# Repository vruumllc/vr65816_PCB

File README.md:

# vr65816

WDC 65C816 Single Board Retro-Computer compatible with [Rumbledethump's Picocomputer Architecture](https://picocomputer.github.io/)

This project is based on [Rumbledethump's Picocomputer 6502 design](https://github.com/picocomputer/schematic), so he gets top billing. 

That said, any flaws are my fault, 'cause his board works GREAT! 

Report any problems to me using the ['Issues'](https://github.com/vruumllc/vr65816_schematic/issues) menu item above.

## Is the vr65816 for you?
Should you be building the vr65816 at all? This board is targeted at experienced programmers interested in exploring and exploiting the 65816 microprocessor. You might want to read the [Caveats](https://github.com/vruumllc/vr65816_schematic/blob/main/README.md#caveats) section at the end of this document before continuing. I built it because I wanted to create projects requiring more memory than the 64kB limit of the 8-bit 6502 processor, and I'm willing to experiment, and fail. 

If you aren't an experienced programmer, or just want to build an inexpensive but extremely capable retro-computer to re-live the exciting early days of the personal computer, then I'd strongly suggest starting with the Rumbledethump's Picocomputer 6502 (RP6502 for short). Order a PCB and support his project [here](https://ko-fi.com/rumbledethumps). 

## My goals for this project
- Use 2 [Rasberry Pi Pico2s](https://www.raspberrypi.com/products/raspberry-pi-pico-2/) with [Rumbledethumps' rp6502 firmware](https://github.com/picocomputer/rp6502)
- Run [WDC 65C816](https://www.westerndesigncenter.com/wdc/documentation/w65c816s.pdf) at up to 8Mhz, clocked by Pico2W RIA
- Use currently produced through-hole ICs only, and no programmable logic
- Use 1MB SRAM, 64kB extended RAM (on Pico2W RIA), and no hardware ROM
- Use [WDC 65C22](https://www.westerndesigncenter.com/wdc/documentation/w65c22s.pdf) for timers and peripheral I/O
- Design, [breadboard](https://github.com/vruumllc/vr65816_schematic/blob/main/images/vr65816_breadboard.jpg), and test it. 
- Run all existing apps and games ("[ROMs](https://discord.com/channels/534571197908647946/1487969279251841216)") for the Rumbledethumps' RP6502 Picocomputer
- Enable [creation](https://github.com/picocomputer/rp6502-sdk) of new "ROMs" utilizing [features and memory of the '816](https://archive.org/details/0893037893ProgrammingThe65816/mode/2up)
- Use [KiCad](https://www.kicad.org/download) to create fully open source schematic and board design files

## Getting the parts
I used [Mouser's 'Create a BOM'](https://www.mouser.com/en/Bom/) feature to order all parts except the PCB.  Use the 'Mouser Part Number' and 'Qty' columns from the [vr65816_full_BOM.csv](https://github.com/vruumllc/vr65816_schematic/blob/main/vr65816_full_BOM.csv) file in this repository.

You can also get the identical parts at [DigiKey](https://www.digikey.com/), except for the WDC 65C816 and 65C22.

My cost per kit of parts was about $124 USD, including shipping, fees, and taxes.

## Getting a PCB
I used [PCBWay](https://www.pcbway.com) to fabricate my PCB:
- Click on "PCB Prototype" at upper left after logging in
- Enter Length=125 and Width=150 mm for the Size
- Select Quantity desired (5 minimum)
- Select Solder Mask and Silkscreen Colors, Surface Finish, and 'Remove Product No.' as desired
- Press the 'Calculate' button at the bottom to generate a price quote
- If the price is right, press 'Save to Cart', then 'Agree' buttons
- Drag the [vr65816_gerbers.zip](https://github.com/vruumllc/vr65816_schematic/blob/main/vr65816_gerbers.zip) file into the web dialog, then click 'Submit the file now'

After a wait of a few minutes while the file is 'Under Review' you will be allowed to place your order.

My cost was about $105 USD including shipping, fees, and taxes -- about $21 USD per PCB.

The total price per vr65816 therefore came out to be about $145 USD (September 2026, Silicon Valley, USA).

## More things you need that you may already own
Rumbledethumps has made a huge effort to support modern hardware, so you don't have to rely on ancient and expensive peripherals to use this retro-computer. Here is a list of peripherals you may already have, with some example links if you don't:

(All links are just clarifying examples and not an endorsement or guarantee of compatibility)

- USB micro-B cable with either [A](https://www.adafruit.com/product/592) or [C](https://www.adafruit.com/product/3878) connector (depending upon what your desktop or laptop computer has)
- [USB-OTG Hub with micro-B connector](https://vilros.com/products/vilros-microusb-to-usb-4-port-otg-hub-black-great-for-pi-zero)
- USB2 flash drive formatted for FAT32 (or 'msdos' in Linux)
- Keyboard, Mouse and [Gamepad](https://www.logitechg.com/en-us/shop/p/f310-gamepad) (USB-2 cable or [wireless](https://www.logitech.com/en-us/shop/p/mk470-slim-wireless-keyboard-mouse), or Bluetooth LE)
- Stereo headphones or computer speakers
- VGA Monitor and cable

  OR
  
- HDMI Monitor, cable, and [VGA to HDMI adapter](https://ventiontech.com/products/vga-to-hdmi-adapter-1080p-vga-male-to-hdmi-female-converter-cable-with-audio-usb-power-for-ps4-3-hdtv-vga-hdmi-converter) (NOT HDMI to VGA adapter!!!)

## Building the vr65816 
On a scale from 1 to 10 for electronics kit build difficulty, the vr65816 ranks about a 3. While it is probably not the best project to learn soldering on, it is an easy kit to build -- well within the capabilities of a supervised middle-school student. The component identifications are all on the back of the PCB, and listed in the [BOM](https://github.com/vruumllc/vr65816_schematic/blob/main/vr65816_full_BOM.csv).

The hardest part is making sure you have the right resisters in the right places (consult a [resister color key](https://en.wikipedia.org/wiki/Electronic_color_code), or use an Ohm meter to make sure). Other than that, just make sure your sockets (and the chips inserted in them) are the correct direction as indicated by the notch on the PCB, and that the 2 LEDs are soldered with the shorter leg (with the flat) in the hole with the square solder pad (cathode in pin1). I guess the middle row of the VGA connector might be a little tricky if you don't have a fine tipped soldering iron...but...you can do this! 

## Uploading the Picocomputer firmware
Get the latest released firmware from [here](https://github.com/picocomputer/rp6502/releases). You want the file named rp6502-#.##-pico.zip, where #.## is the latest version number. 
- Unzip the files to a temporary folder on your host computer
- Plug the micro-B USB cable into the Pico 2W (the one with the rectangular metal shield around the wireless chip)
- Press and hold the BootSel button on the Pico 2W, then plug the other end of the cable into your host computer
- Release the BootSel button, and you should see a new drive appear on your host computer
- Copy (or drag) the rp6502-#.##-ria-w.uf2 file into the new drive
- The file should upload to the Pico 2W and turn it into the "RIA", lighting the LED.
- Repeat the process for the Pico 2, this time copying the rp6502-#.##-vga.uf2, creating the 'VGA card' for the vr65816.
- Unplug the USB cable from your host computer, leaving it connected to the Pico 2 VGA micro-B port

## Testing your vr65816
OK! You should now have a completed vr65816 retro-computer of your very own. Let's test it.
- Plug the USB 2 OTG hub into the micro-B port of the Pico 2W RIA
- On your host computer, copy the [test "ROM" files](https://github.com/vruumllc/vr65816_schematic/tree/main/test_ROMS) (ending in .rp6502 or .vr65816) from this repository into the USB flash drive
- Remove the USB flash drive from your host computer and plug it into the USB 2 OTG hub
- Plug in any other USB 2 peripherals like keyboard, mouse, and gamepad, if you have them
- Plug in the headphones or computer speakers, if you have them
- Plug in the video monitor if you have it, using the VGA to HDMI adapter if it is an HDMI monitor
- Finally, plug the USB cable connected to the Pico 2 VGA back into your host computer.

If you have a video monitor connected, you should see "Picocomputer 6502" and the RIA and VGA firmware versions you uploaded, followed by the prompt ']' and a blinking cursor.

If you don't have monitor, keyboard, mouse, gamepad, or speakers yet, don't worry.  You can still continue testing as long as you have the USB cable connected from the Pico 2 VGA to your host computer.  Besides powering the vr65816, this cable supplies a serial communication channel operating at 115200 baud, 8 data bits, 1 stop bit, no parity, and no flow control. You can use a serial terminal program on your host computer to interact with the vr65816. The details vary depending upon your host computer type. I use Linux and like GTKTerm. PuttySSH also works well and exists for both Linux and Windows. Sorry, I've never owned a Mac, so you are on your own.

If you've arrived at the ']', you've verified that the Pico half of the vr65816 is working.  You are looking at the prompt for the 'monitor' program (not to be confused with a computer display), which runs on the Pico 2W RIA. Try typing "help" to see all that it can do for you. 

You still haven't tested the 65816 half of the board, however. To do that, simply type "0" and return.  You should see the contents of the first 16 bytes of the 65816 memory, thus verifying that the RIA can talk to the 65816 microprocessor and access its memory.

Congratulations! Time to start having fun by loading some ROMs.

## Caveats
Rumbledethump's Picocomputer Architecture for the WDC 65C02 was developed over several YEARS and encompasses not just the RP6502 hardware and its firmware, but platform support on two C compilers, and a programming infrastructure developed for Microsoft's Visual Studio Code IDE (not to mention the emulators, FPGA implementation...).

All of this is a wonderful base for my project, but I went into it knowing that since it was developed for the 6502, that there would some limitations re-using it. I had NO intentions of forking any of his architecture, and instead would learn to work within the limitations. You should too. 

Here are some things to keep in mind before building my vr65816:

1. Rumbledethump has stated that he has no interest in the 65816. That means the vr65816 is a kind of a, umm, love child of his efforts. Please don't ask him to add any new features in support of this project.
2. Similarly, be considerate at the [Picocomputer 6502 Discord site](https://discord.com/channels/534571197908647946/1545859287706902559). Rumbledethumps has created an '#other-hardware' channel for projects like mine. Please use it. I'll keep on eye on it.
3. Very importantly, neither C compiler supporting the RP6502 compiles for the 65816. The ca65 assembler piece of the [cc65 project](https://cc65.github.io/) DOES understand 65816 assembly, though, as does [llvm-mos's](https://llvm-mos.org/wiki/Welcome) assembler. This means that to exploit the 16-bit features and memory of the vr65816, you will need to code in assembly language. I plan to put 'best practice' examples in the [vr65816_examples](https://github.com/vruumllc/vr65816_examples) repository. I could really use help developing these, as I know relatively little about assembly language programming.
4. Unfortunately, the 6502 memory locations reserved for the 'RIA registers', used to communicate between the Pico 2W RIA and the 6502, overlap the 65816 16-bit interrupt vectors. That limits us to throwing interrupts only while in 8-bit mode. As a very last resort, I added the mysterious jumper JP4, which increases the space for the RIA registers enough to shift them down. This would mean #defining all the register locations in the firmware and compilers, and breaking compatibility with 6502 ROMs, which I really, really, really don't want to do.
5. The RIA can only access the lowest 64kB of memory, so each 65816 ROM will have to be responsible for loading its assets and code into higher memory. Large 65816 projects will need to be designed so that the initially loaded portion is less than 64kB.
6. 65816 ROMs will have to check programatically to make sure they are not accidentally loaded into an RP6502. The ROMS must exit gracefully with a message if so. The monitor program handles loading ROMs renamed to have a .vr65816 extension, so that might help to avoid confusion.
7. The monitor program can only dump the lowest 64kB of microcontroller memory (65816 Bank0), and displays the 64kB of extended RAM living on the RIA using the 65816 Bank1 addresses. Confusing, but if dumping any 65816 upper memory is needed, a 65816-specific ROM can be written.
8. The emulators written thus far only support the RP6502.
9. The vr65816 PCB is 25mm taller than the RP6502 PCB, so it won't fit in the fabulous 3D-printed cases I've already designed. If I ever finish working on this README and the vr65816_examples, I'll hop right to it and come up with something special.
10. I'm sure more things will come to light...

Don't get too discouraged by all this. At the very least you'll wind up with a retro-computer compatible with the RP6502, which (have I already mentioned this?) is really GREAT!

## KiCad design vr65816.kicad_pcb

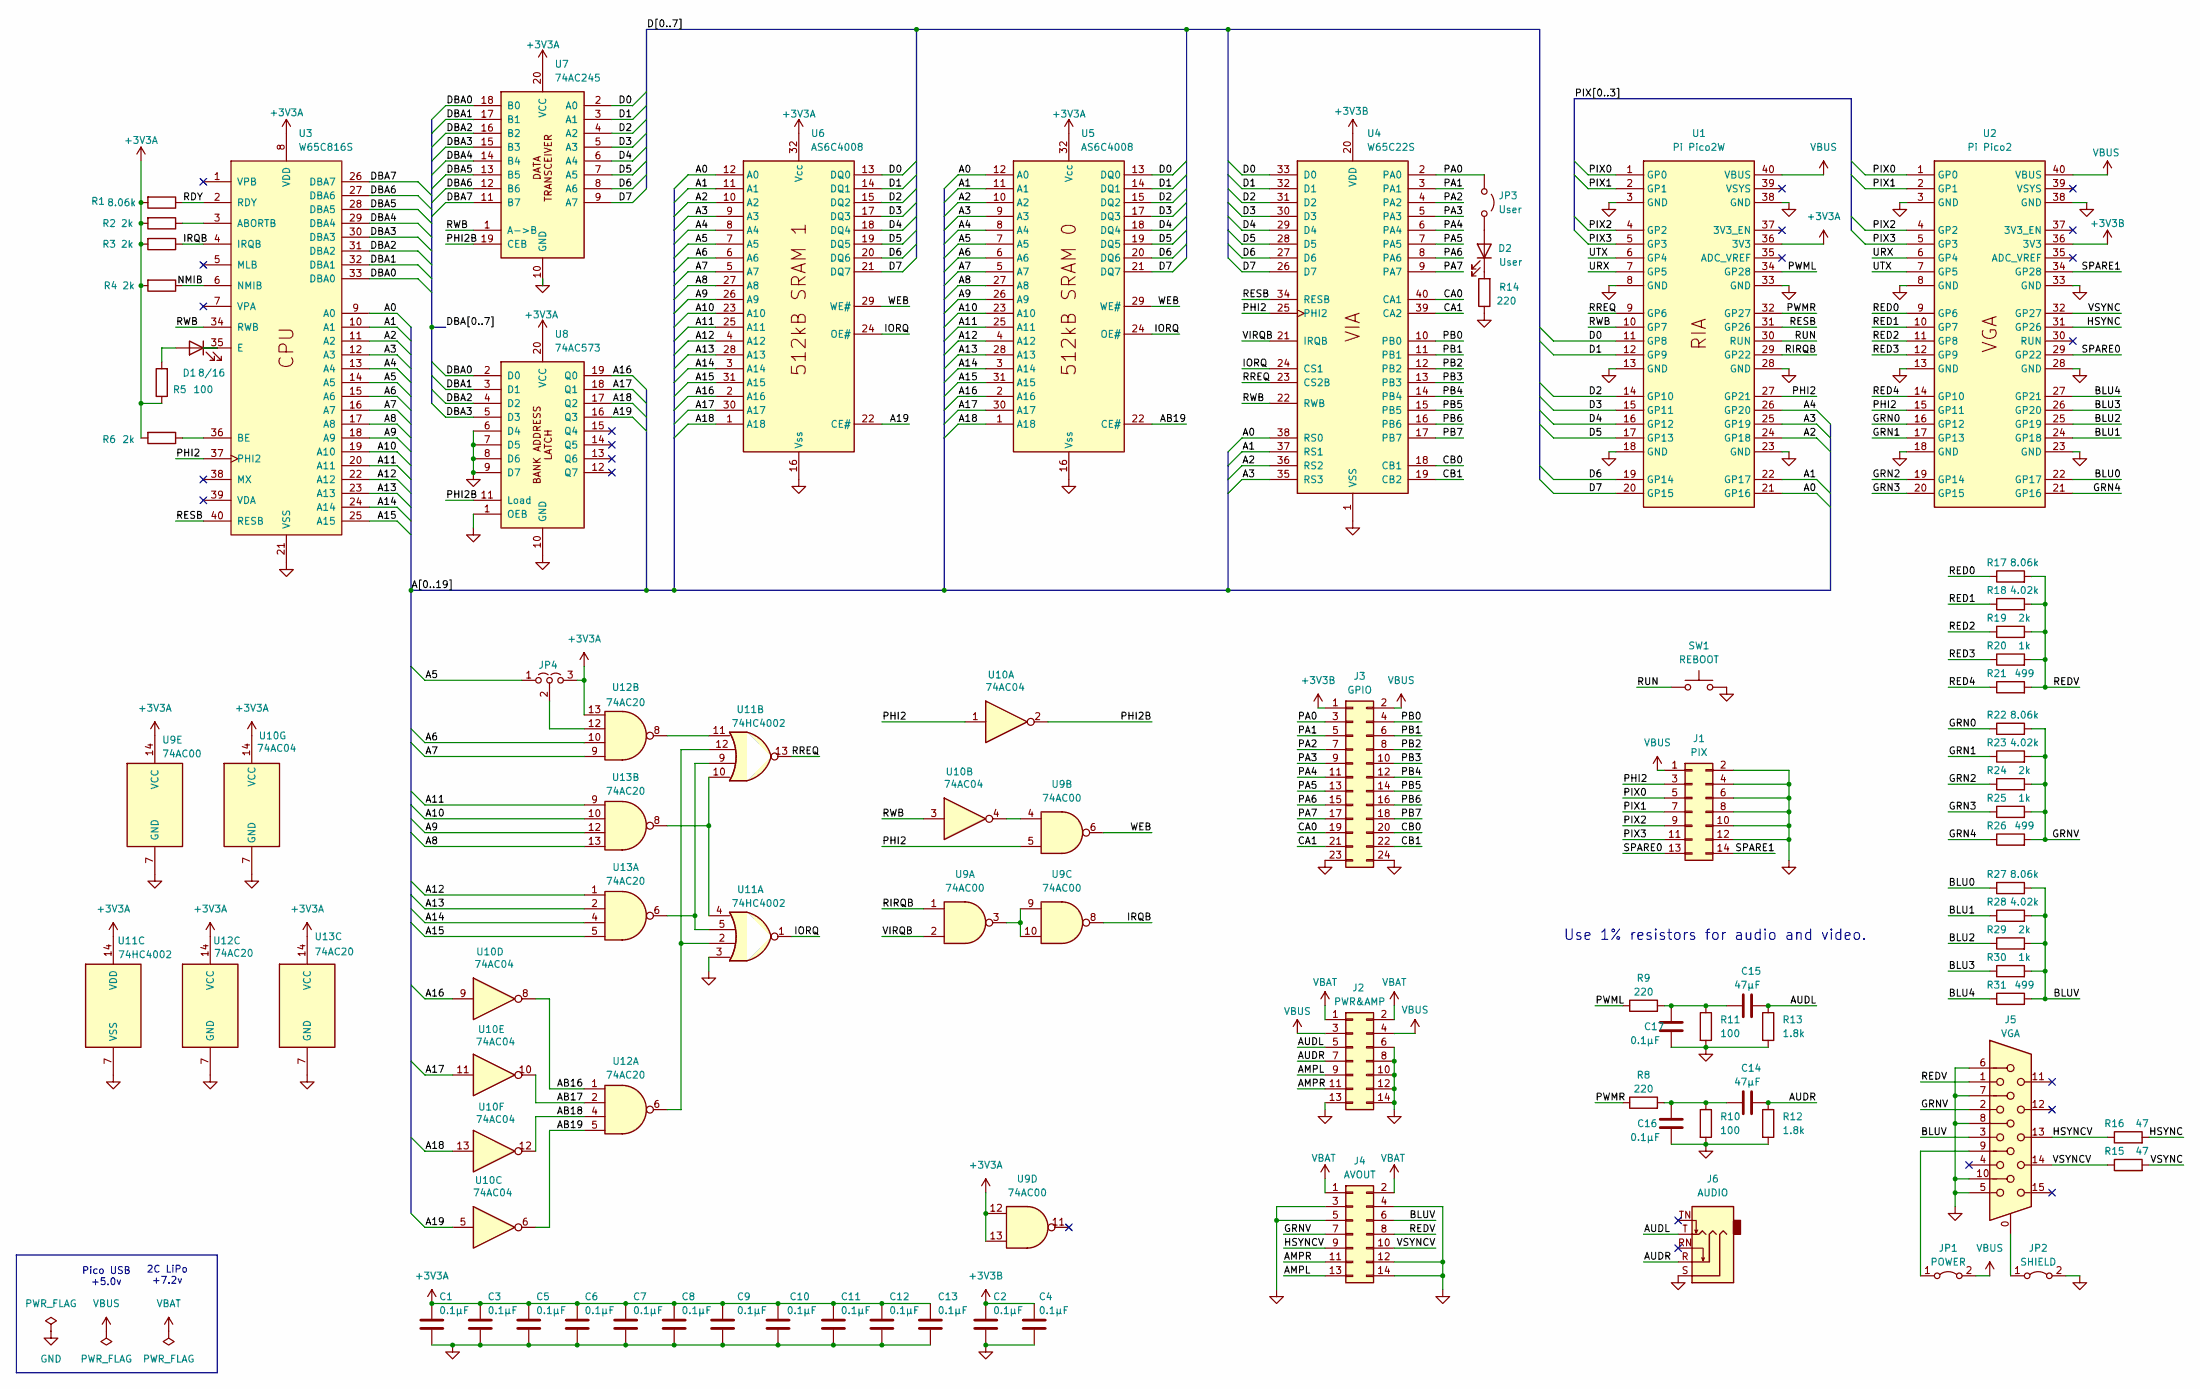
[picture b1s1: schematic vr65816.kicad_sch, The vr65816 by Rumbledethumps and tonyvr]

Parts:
C1, C2, C3, C4, C5, C6, C7, C8, C9, C10, C11, C12, C13, C16, C17: 0.1μF; R_Axial_DIN0207_L6.3mm_D2.5mm_P10.16mm_Horizontal_Long
C14, C15: 47μF; C_Disc_D7.5mm_W5.0mm_P5.00mm_Long
D1: 8/16; LED_D3.0mm
D2: User; LED_D3.0mm
J1: PIX; PinHeader_2x07_P2.54mm_Vertical
J2: PWR&AMP; PinHeader_2x07_P2.54mm_Vertical
J3: GPIO; PinHeader_2x12_P2.54mm_Vertical
J4: AVOUT; PinHeader_2x07_P2.54mm_Vertical
J5: VGA; DSUB-15-HD_Female_Horizontal_P2.29x2.54mm_EdgePinOffset8.35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
J6: AUDIO; Jack_3.5mm_CUI_SJ1-3525N_Horizontal
JP1: POWER; SolderJumper-2_P1.3mm_Bridged2Bar_RoundedPad1.0x1.5mm
JP2: SHIELD; SolderJumper-2_P1.3mm_Bridged2Bar_RoundedPad1.0x1.5mm
JP3: User; PinHeader_1x02_P2.54mm_Vertical
JP4: 3,[2,1]; PinHeader_1x03_P2.54mm_Vertical
R1, R17, R22, R27: 8.06k; R_Axial_DIN0207_L6.3mm_D2.5mm_P10.16mm_Horizontal_Long
R2, R3, R4, R6, R19, R24, R29: 2k; R_Axial_DIN0207_L6.3mm_D2.5mm_P10.16mm_Horizontal_Long
R5, R10, R11: 100; R_Axial_DIN0207_L6.3mm_D2.5mm_P10.16mm_Horizontal_Long
R8, R9, R14: 220; R_Axial_DIN0207_L6.3mm_D2.5mm_P10.16mm_Horizontal_Long
R12, R13: 1.8k; R_Axial_DIN0207_L6.3mm_D2.5mm_P10.16mm_Horizontal_Long
R15, R16: 47; R_Axial_DIN0207_L6.3mm_D2.5mm_P10.16mm_Horizontal_Long
R18, R23, R28: 4.02k; R_Axial_DIN0207_L6.3mm_D2.5mm_P10.16mm_Horizontal_Long
R20, R25, R30: 1k; R_Axial_DIN0207_L6.3mm_D2.5mm_P10.16mm_Horizontal_Long
R21, R26, R31: 499; R_Axial_DIN0207_L6.3mm_D2.5mm_P10.16mm_Horizontal_Long
SW1: REBOOT; SW_Tactile_SKHH_Angled
U1: Pi Pico2W; DIP-40_W17.78mm_LongPads
U2: Pi Pico2; DIP-40_W17.78mm_LongPads
U3: W65C816S; DIP-40_W15.24mm_LongPads
U4: W65C22S; DIP-40_W15.24mm_LongPads
U5, U6: AS6C4008; DIP-32_W15.24mm_LongPads
U7: 74AC245; DIP-20_W7.62mm_LongPads
U8: 74AC573; DIP-20_W7.62mm_LongPads
U9: 74AC00; DIP-14_W7.62mm_LongPads
U10: 74AC04; DIP-14_W7.62mm_LongPads
U11: 74HC4002; DIP-14_W7.62mm_LongPads
U12, U13: 74AC20; DIP-14_W7.62mm_LongPads

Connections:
+3V3A: C1.1, C3.1, C5.1, C6.1, C7.1, C8.1, C9.1, C10.1, C11.1, C12.1, C13.1, JP4.3 (B), R1.2, R2.2, R3.2, R4.2, R5.1, R6.2, U1.36 (3V3), U3.8 (VDD), U5.32 (Vcc), U6.32 (Vcc), U7.20 (VCC), U8.20 (VCC), U9.12, U9.13, U9.14 (VCC), U10.14 (VCC), U11.14 (VDD), U12.13, U12.14 (VCC), U13.14 (VCC)
+3V3B: C2.1, C4.2, J3.1, U2.36 (3V3), U4.20 (VDD)
/A0: U1.21 (GP16), U3.9 (A0), U4.38 (RS0), U5.12 (A0), U6.12 (A0)
/A1: U1.22 (GP17), U3.10 (A1), U4.37 (RS1), U5.11 (A1), U6.11 (A1)
/A2: U1.24 (GP18), U3.11 (A2), U4.36 (RS2), U5.10 (A2), U6.10 (A2)
/A3: U1.25 (GP19), U3.12 (A3), U4.35 (RS3), U5.9 (A3), U6.9 (A3)
/A4: U1.26 (GP20), U3.13 (A4), U5.8 (A4), U6.8 (A4)
/A5: JP4.1 (A), U3.14 (A5), U5.7 (A5), U6.7 (A5)
/A6: U3.15 (A6), U5.6 (A6), U6.6 (A6), U12.10
/A7: U3.16 (A7), U5.5 (A7), U6.5 (A7), U12.9
/A8: U3.17 (A8), U5.27 (A8), U6.27 (A8), U13.13
/A9: U3.18 (A9), U5.26 (A9), U6.26 (A9), U13.12
/A10: U3.19 (A10), U5.23 (A10), U6.23 (A10), U13.10
/A11: U3.20 (A11), U5.25 (A11), U6.25 (A11), U13.9
/A12: U3.22 (A12), U5.4 (A12), U6.4 (A12), U13.1
/A13: U3.23 (A13), U5.28 (A13), U6.28 (A13), U13.2
/A14: U3.24 (A14), U5.3 (A14), U6.3 (A14), U13.4
/A15: U3.25 (A15), U5.31 (A15), U6.31 (A15), U13.5
/A16: U5.2 (A16), U6.2 (A16), U8.19 (Q0), U10.9
/A17: U5.30 (A17), U6.30 (A17), U8.18 (Q1), U10.11
/A18: U5.1 (A18), U6.1 (A18), U8.17 (Q2), U10.13
/A19: U6.22 (CE#), U8.16 (Q3), U10.5
/AB16: U10.8, U12.1
/AB17: U10.10, U12.2
/AB18: U10.12, U12.4
/AB19: U5.22 (CE#), U10.6, U12.5
/AMPL: J2.9, J4.13
/AMPR: J2.11, J4.11
/AUDL: C15.2, J2.5, J6.T, R13.1
/AUDR: C14.2, J2.7, J6.R, R12.1
/BLU0: R27.1, U2.22 (GP17)
/BLU1: R28.1, U2.24 (GP18)
/BLU2: R29.1, U2.25 (GP19)
/BLU3: R30.1, U2.26 (GP20)
/BLU4: R31.1, U2.27 (GP21)
/BLUV: J4.6, J5.3, R27.2, R28.2, R29.2, R30.2, R31.2
/CA0: J3.19, U4.40 (CA1)
/CA1: J3.21, U4.39 (CA2)
/CB0: J3.20, U4.18 (CB1)
/CB1: J3.22, U4.19 (CB2)
/D0: U1.11 (GP8), U4.33 (D0), U5.13 (DQ0), U6.13 (DQ0), U7.2 (A0)
/D1: U1.12 (GP9), U4.32 (D1), U5.14 (DQ1), U6.14 (DQ1), U7.3 (A1)
/D2: U1.14 (GP10), U4.31 (D2), U5.15 (DQ2), U6.15 (DQ2), U7.4 (A2)
/D3: U1.15 (GP11), U4.30 (D3), U5.17 (DQ3), U6.17 (DQ3), U7.5 (A3)
/D4: U1.16 (GP12), U4.29 (D4), U5.18 (DQ4), U6.18 (DQ4), U7.6 (A4)
/D5: U1.17 (GP13), U4.28 (D5), U5.19 (DQ5), U6.19 (DQ5), U7.7 (A5)
/D6: U1.19 (GP14), U4.27 (D6), U5.20 (DQ6), U6.20 (DQ6), U7.8 (A6)
/D7: U1.20 (GP15), U4.26 (D7), U5.21 (DQ7), U6.21 (DQ7), U7.9 (A7)
/DBA0: U3.33 (DBA0), U7.18 (B0), U8.2 (D0)
/DBA1: U3.32 (DBA1), U7.17 (B1), U8.3 (D1)
/DBA2: U3.31 (DBA2), U7.16 (B2), U8.4 (D2)
/DBA3: U3.30 (DBA3), U7.15 (B3), U8.5 (D3)
/DBA4: U3.29 (DBA4), U7.14 (B4)
/DBA5: U3.28 (DBA5), U7.13 (B5)
/DBA6: U3.27 (DBA6), U7.12 (B6)
/DBA7: U3.26 (DBA7), U7.11 (B7)
/GRN0: R22.1, U2.16 (GP12)
/GRN1: R23.1, U2.17 (GP13)
/GRN2: R24.1, U2.19 (GP14)
/GRN3: R25.1, U2.20 (GP15)
/GRN4: R26.1, U2.21 (GP16)
/GRNV: J4.7, J5.2, R22.2, R23.2, R24.2, R25.2, R26.2
/HSYNC: R16.2, U2.31 (GP26)
/HSYNCV: J4.9, J5.13, R16.1
/IORQ: U4.24 (CS1), U5.24 (OE#), U6.24 (OE#), U11.1
/IRQB: R3.1, U3.4 (IRQB), U9.8
/NMIB: R4.1, U3.6 (NMIB)
/PA0: J3.3, JP3.1 (A), U4.2 (PA0)
/PA1: J3.5, U4.3 (PA1)
/PA2: J3.7, U4.4 (PA2)
/PA3: J3.9, U4.5 (PA3)
/PA4: J3.11, U4.6 (PA4)
/PA5: J3.13, U4.7 (PA5)
/PA6: J3.15, U4.8 (PA6)
/PA7: J3.17, U4.9 (PA7)
/PB0: J3.4, U4.10 (PB0)
/PB1: J3.6, U4.11 (PB1)
/PB2: J3.8, U4.12 (PB2)
/PB3: J3.10, U4.13 (PB3)
/PB4: J3.12, U4.14 (PB4)
/PB5: J3.14, U4.15 (PB5)
/PB6: J3.16, U4.16 (PB6)
/PB7: J3.18, U4.17 (PB7)
/PHI2: J1.3, U1.27 (GP21), U2.15 (GP11), U3.37 (PHI2), U4.25 (PHI2), U9.5, U10.1
/PHI2B: U7.19 (CEB), U8.11 (Load), U10.2
/PIX0: J1.5, U1.1 (GP0), U2.1 (GP0)
/PIX1: J1.7, U1.2 (GP1), U2.2 (GP1)
/PIX2: J1.9, U1.4 (GP2), U2.4 (GP2)
/PIX3: J1.11, U1.5 (GP3), U2.5 (GP3)
/PWML: R9.1, U1.34 (GP28)
/PWMR: R8.1, U1.32 (GP27)
/RDY: R1.1, U3.2 (RDY)
/RED0: R17.1, U2.9 (GP6)
/RED1: R18.1, U2.10 (GP7)
/RED2: R19.1, U2.11 (GP8)
/RED3: R20.1, U2.12 (GP9)
/RED4: R21.1, U2.14 (GP10)
/REDV: J4.8, J5.1, R17.2, R18.2, R19.2, R20.2, R21.2
/RESB: U1.31 (GP26), U3.40 (RESB), U4.34 (RESB)
/RIRQB: U1.29 (GP22), U9.1
/RREQ: U1.9 (GP6), U4.23 (CS2B), U11.13
/RUN: SW1.2, U1.30 (RUN)
/RWB: U1.10 (GP7), U3.34 (RWB), U4.22 (RWB), U7.1 (A->B), U10.3
/SPARE0: J1.13, U2.29 (GP22)
/SPARE1: J1.14, U2.34 (GP28)
/URX: U1.7 (GP5), U2.6 (GP4)
/UTX: U1.6 (GP4), U2.7 (GP5)
/VIRQB: U4.21 (IRQB), U9.2
/VSYNC: R15.2, U2.32 (GP27)
/VSYNCV: J4.10, J5.14, R15.1
/WEB: U5.29 (WE#), U6.29 (WE#), U9.6
GND: C1.2, C2.2, C3.2, C4.1, C5.2, C6.2, C7.2, C8.2, C9.2, C10.2, C11.2, C12.2, C13.2, C16.2, C17.2, J1.2, J1.4, J1.6, J1.8, J1.10, J1.12, J2.6, J2.8, J2.10, J2.12, J2.13, J2.14, J3.23, J3.24, J4.3, J4.4, J4.5, J4.12, J4.14, J5.5, J5.6, J5.7, J5.8, J5.10, J6.S, JP2.2 (B), R10.2, R11.2, R12.2, R13.2, R14.1, SW1.1, U1.3 (GND), U1.8 (GND), U1.13 (GND), U1.18 (GND), U1.23 (GND), U1.28 (GND), U1.33 (GND), U1.38 (GND), U2.3 (GND), U2.8 (GND), U2.13 (GND), U2.18 (GND), U2.23 (GND), U2.28 (GND), U2.33 (GND), U2.38 (GND), U3.21 (VSS), U4.1 (VSS), U5.16 (Vss), U6.16 (Vss), U7.10 (GND), U8.1 (OEB), U8.6 (D4), U8.7 (D5), U8.8 (D6), U8.9 (D7), U8.10 (GND), U9.7 (GND), U10.7 (GND), U11.3, U11.7 (VSS), U12.7 (GND), U13.7 (GND)
unnamed: C14.1, C16.1, R8.2, R10.1
unnamed: C15.1, C17.1, R9.2, R11.1
unnamed: D1.2 (A), R5.2
unnamed: D1.1 (K), U3.35 (E)
unnamed: D2.2 (A), JP3.2 (B)
unnamed: D2.1 (K), R14.2
unnamed: J5.9, JP1.1 (A)
unnamed: J5.0, JP2.1 (A)
unnamed: JP4.2 (C), U12.12
unnamed: R2.1, U3.3 (ABORTB)
unnamed: R6.1, U3.36 (BE)
unnamed: U9.3, U9.9, U9.10
unnamed: U9.4, U10.4
unnamed: U11.5, U11.9, U13.6
unnamed: U11.4, U11.10, U13.8
unnamed: U11.11, U12.8
unnamed: U11.2, U11.12, U12.6
VBAT: J2.1, J2.2, J4.1, J4.2
VBUS: J1.1, J2.3, J2.4, J3.2, JP1.2 (B), U1.40 (VBUS), U2.40 (VBUS)

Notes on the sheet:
Use 1% resistors for audio and video.
Pico USB +5.0v
2C LiPo +7.2v

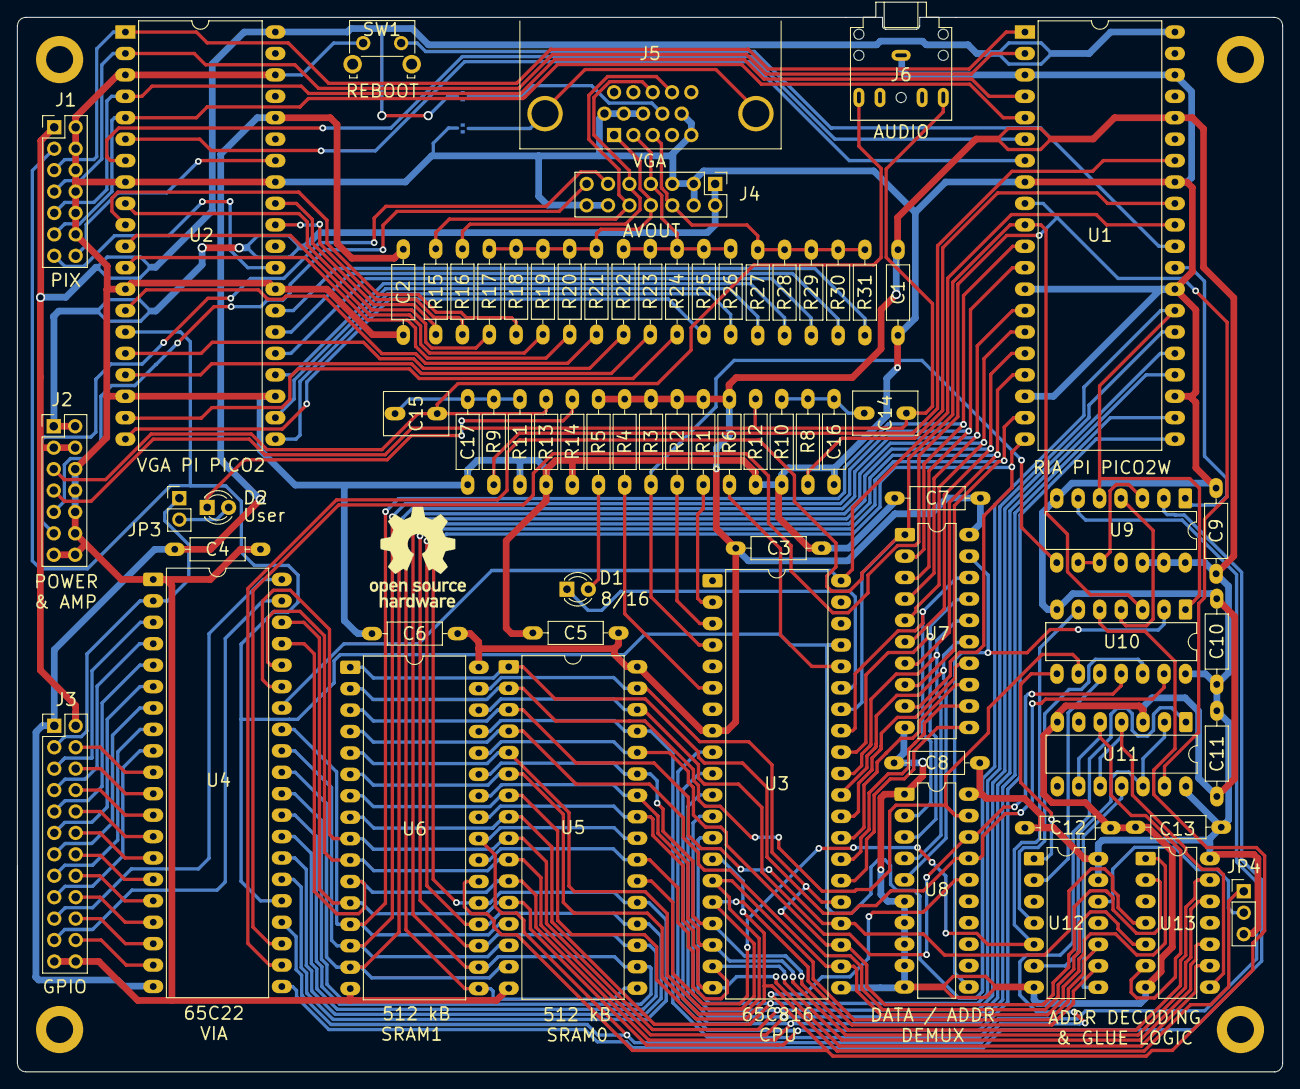
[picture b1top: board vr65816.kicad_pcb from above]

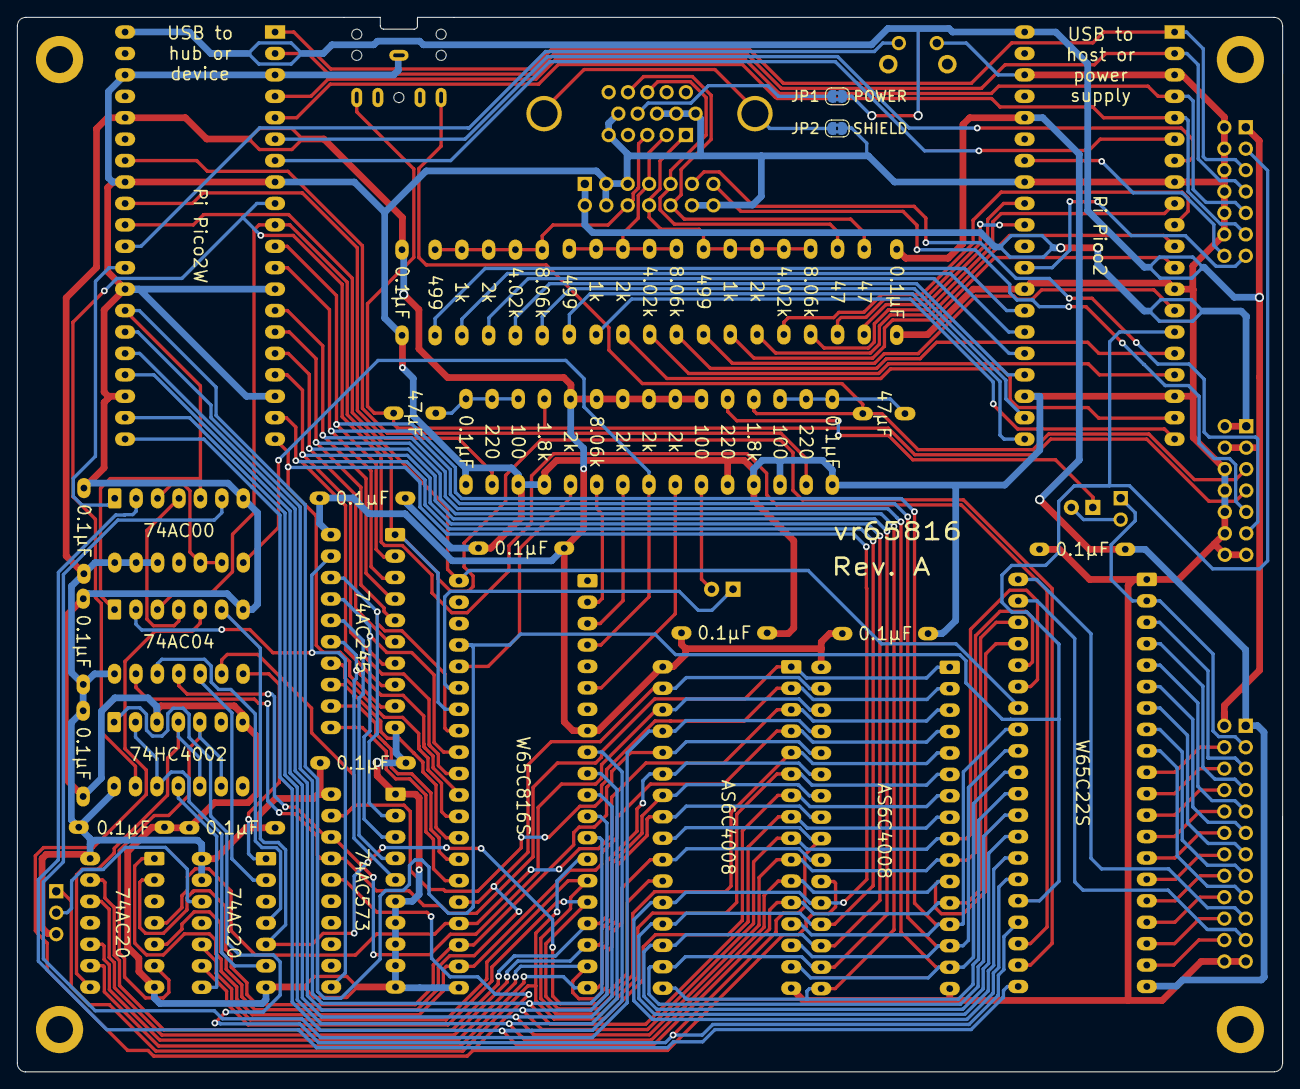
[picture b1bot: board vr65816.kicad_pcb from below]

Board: 2 copper layers, 150.0 x 125.0 mm, 73 parts (2 on the bottom side), 131 nets.

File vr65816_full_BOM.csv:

Qty,Reference,Description,Mfr Name,Mfr Part Number,Mouser Part Number
15,"C1, C2, C3, C4, C5, C6, C7, C8, C9, C10, C11, C12, C13, C16, C17",0.1μF Ceramic Capacitor,Vishay,A104M15X7RF5TAA,594-A104M15X7RF5TAA
2,"C14, C15",47μF Ceramic Capacitor,TDK,FG22X5R1A476MNT06,810-FG22X5R1A476MNT6
1,D1,"3.0mm LED, yellow",Vishay,TLLY4400,78-TLLY4400
1,D2,"3.0mm LED, green",Vishay,TLLG4400,78-TLLG4400
4,"R1,R17, R22, R27",8.06k resistor 1%,YAGEO,MFR-25FBF52-8K06,603-MFR-25FBF52-8K06
3,"R18, R23, R28",4.02k resistor 1%,YAGEO,MFR-25FBF52-4K02,603-MFR-25FBF52-4K02
7,"R2, R3, R4, R6, R19, R24, R29",2k resistor 1%,YAGEO,MFR-25FBF52-2K,603-MFR-25FBF52-2K
2,"R12, R13",1.8k resistor 1%,YAGEO,MFR-25FBF52-1K8,603-MFR-25FBF52-1K8
3,"R20, R25, R30",1k resistor 1%,YAGEO,MFR-25FBF52-1K,603-MFR-25FBF52-1K
3,"R21, R26, R31",499 ohm resistor 1%,YAGEO,MFR-25FBF52-499R,603-MFR-25FBF52-499R
3,"R8, R9, R14",220 ohm resistor 1%,YAGEO,MFR-25FBF52-220R,603-MFR-25FBF52-220R
3,"R5, R10, R11",100 ohm resistor 1%,YAGEO,MFR-25FBF52-100R,603-MFR-25FBF52-100R
2,"R15, R16",47 ohm resistor 1%,YAGEO,MFR-25FBF52-47R,603-MFR-25FBF52-47R
1,U3,WDC W65C816S,WDC,W65C816S6PG-14,955-W65C816S6PG-14
1,U4,WDC W65C22S,WDC,W65C22S6TPG-14,955-W65C22S6TPG-14
2,"U5,U6",512k SRAM AS6C4008,Alliance,AS6C4008-55PCN,913-AS6C4008-55PCN
1,U7,74AC245 Octal Tri-State Bus Transceiver,TI,CD74AC245E,595-CD74AC245E
1,U8,"74AC573 Octal Transparent Latch, 3-State",TI,CD74AC573E,595-CD74AC573E
1,U9,74AC00 Quad NAND,TI,CD74AC00E,595-CD74AC00E
1,U10,74AC04 Hex Inverter,TI,CD74AC04E,595-CD74AC04E
1,U11,74HC4002 Dual 4 input NOR,TI,CD74HC4002E,595-CD74HC4002E
2,"U12, U13",74AC20 Dual 4 Input NAND,TI,CD74AC20E,595-CD74AC20E
3,"J1,J2,J4","PIX,PWR&AMP,AVOUT 2x8 Pin headers",Amp,10129381-914001BLF,649-1012938191401BLF
1,J3,GPIO 2x12 Pin Header,Amp,10129381-924001BLF,649-1012938192401BLF
1,JP4,1x2 Jumper,Amp,10129378-902003BLF,649-1012937890203BLF
1,JP3,1x3 Jumper,Amp,10129378-903003BLF,649-1012937890303BLF
2,"JP3,JP4",Jumper Socket,Harwin,855-M7567-46,855-M7567-46
4,"U1,U2",Pico 20 Pin Socket,Wurth,61302011821,710-61302011821
1,J3,VGA Jack,Amp,L77HDE15SD1CH4FVGA,523-7HDE15SD1CH4FVGA
1,J4,Audio Jack,CUI,SJ1-3525NG-GR,490-SJ1-3525NG-GR
1,SW1,Reset Button,CUI,TS11-674-43-BK-160-RA-D,179-TS1167443160RAD
5,"U9, U10,U11,U12,U13",14-pin IC Socket,TE,1-2199298-3,571-1-2199298-3
1,U8,16-pin IC Socket,TE,1-2199298-4,571-1-2199298-4
1,U7,20-pin IC Socket,TE,1-2199298-6,571-1-2199298-6
2,"U5,U6",32-pin IC Socket,TE,1-2199300-2,571-1-2199300-2
2,"U3,U4",40-pin IC Socket,TE,1-2199299-5,571-1-2199299-5
4,PCB,Stick-on Bumper Feet,Essentra,ASPR-8-125,144-ASPR-8-125
